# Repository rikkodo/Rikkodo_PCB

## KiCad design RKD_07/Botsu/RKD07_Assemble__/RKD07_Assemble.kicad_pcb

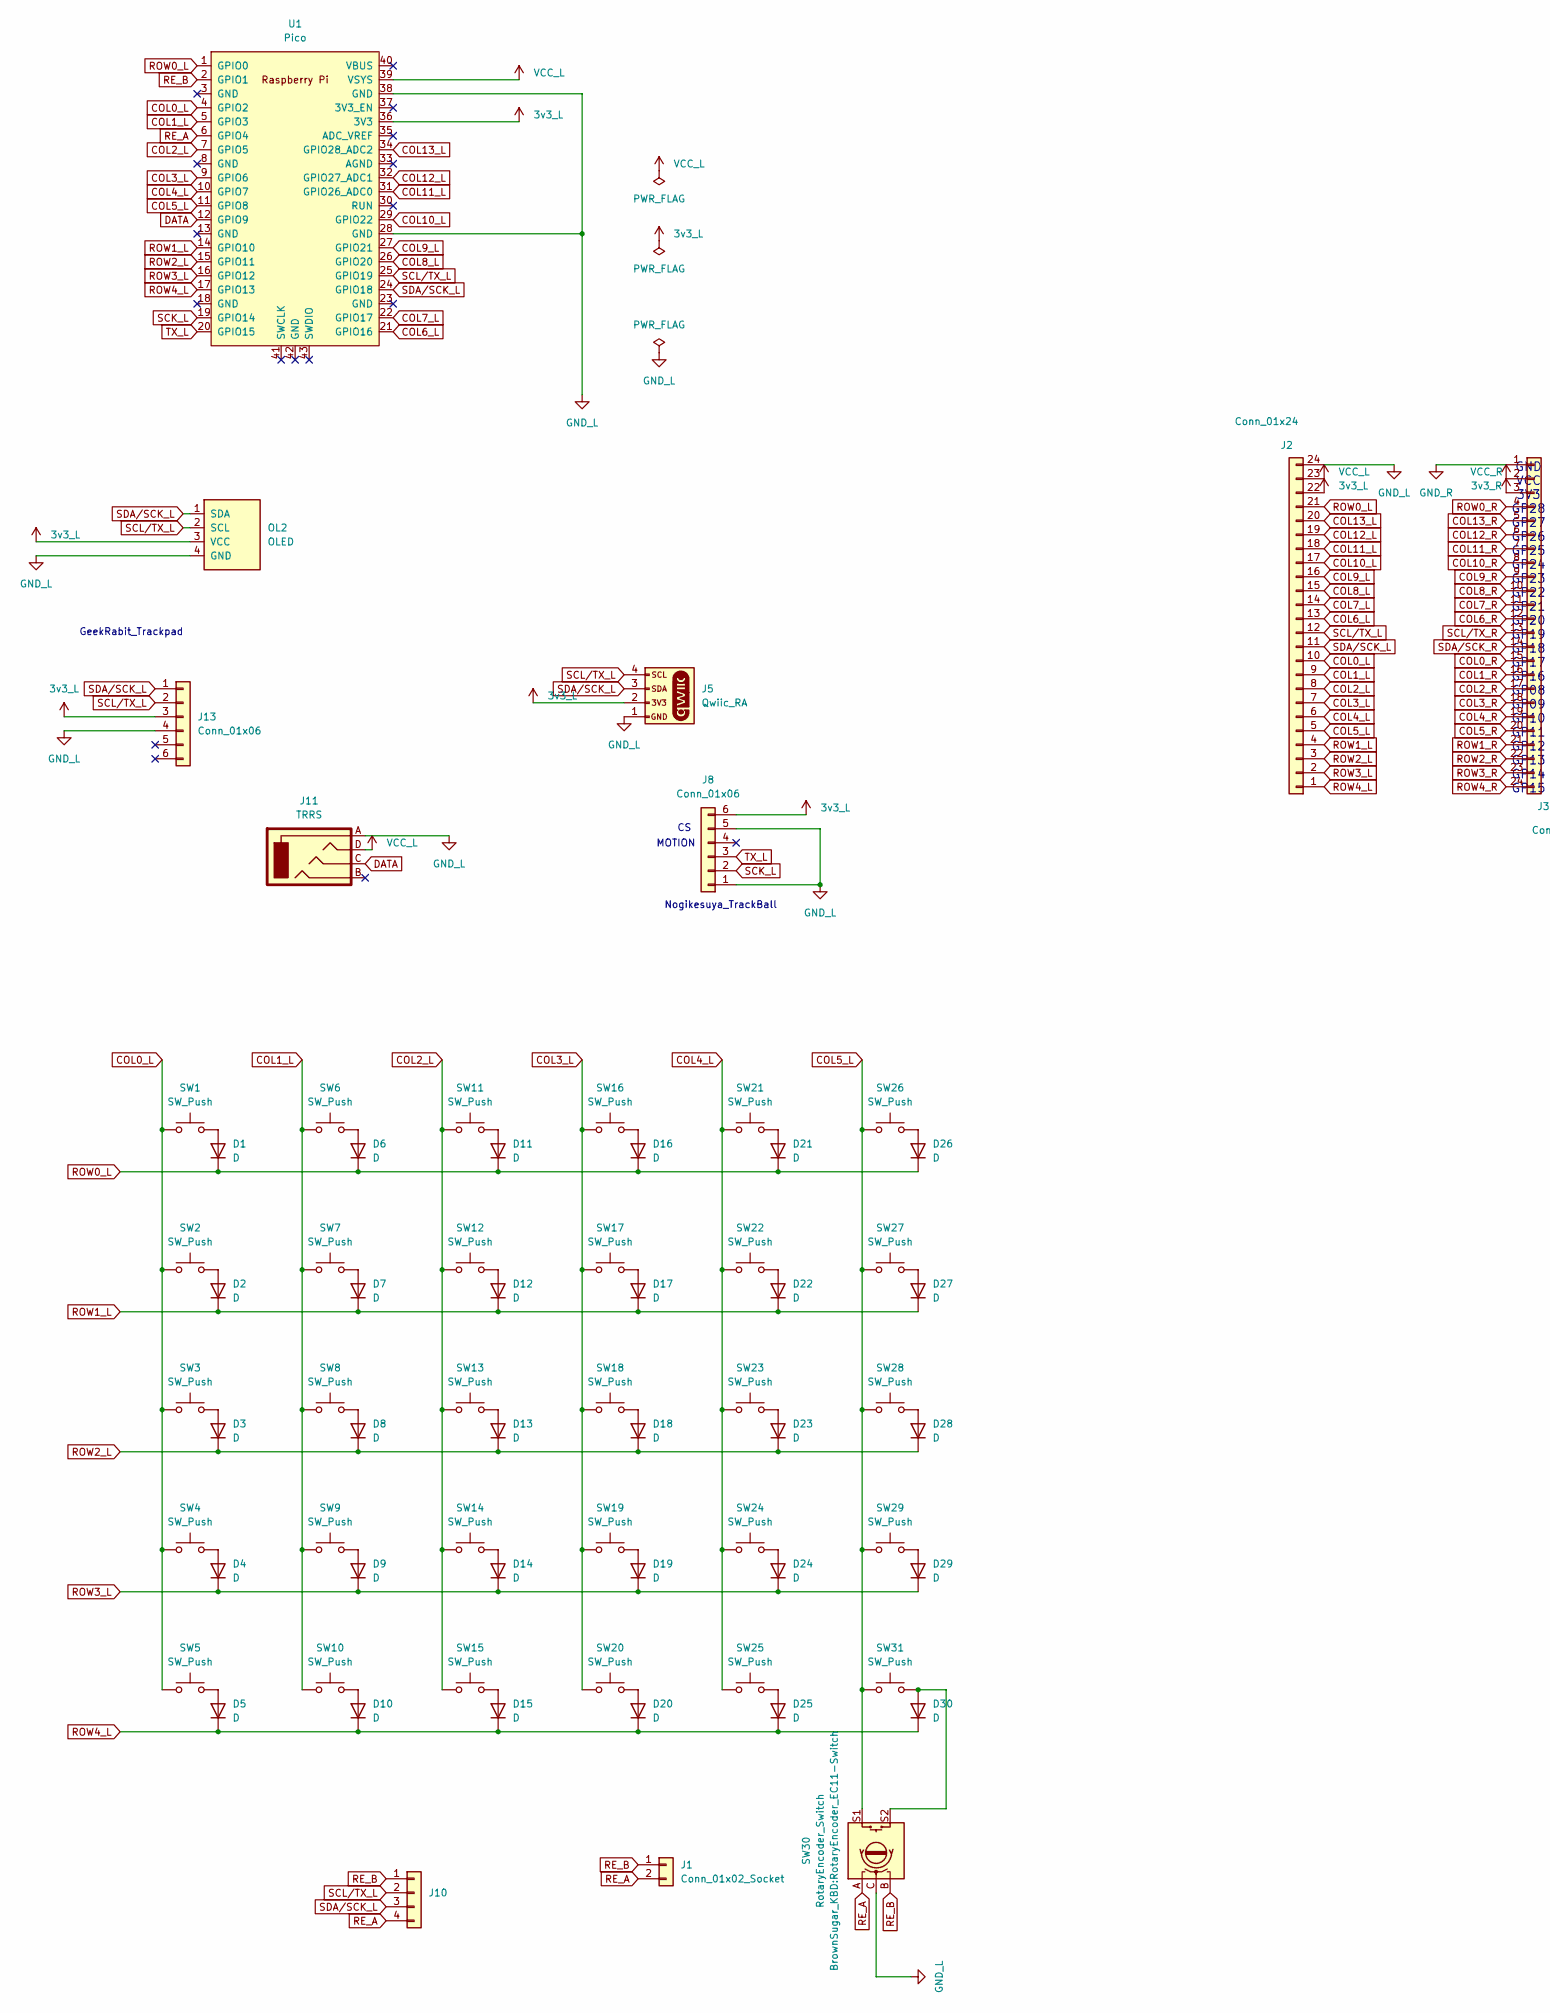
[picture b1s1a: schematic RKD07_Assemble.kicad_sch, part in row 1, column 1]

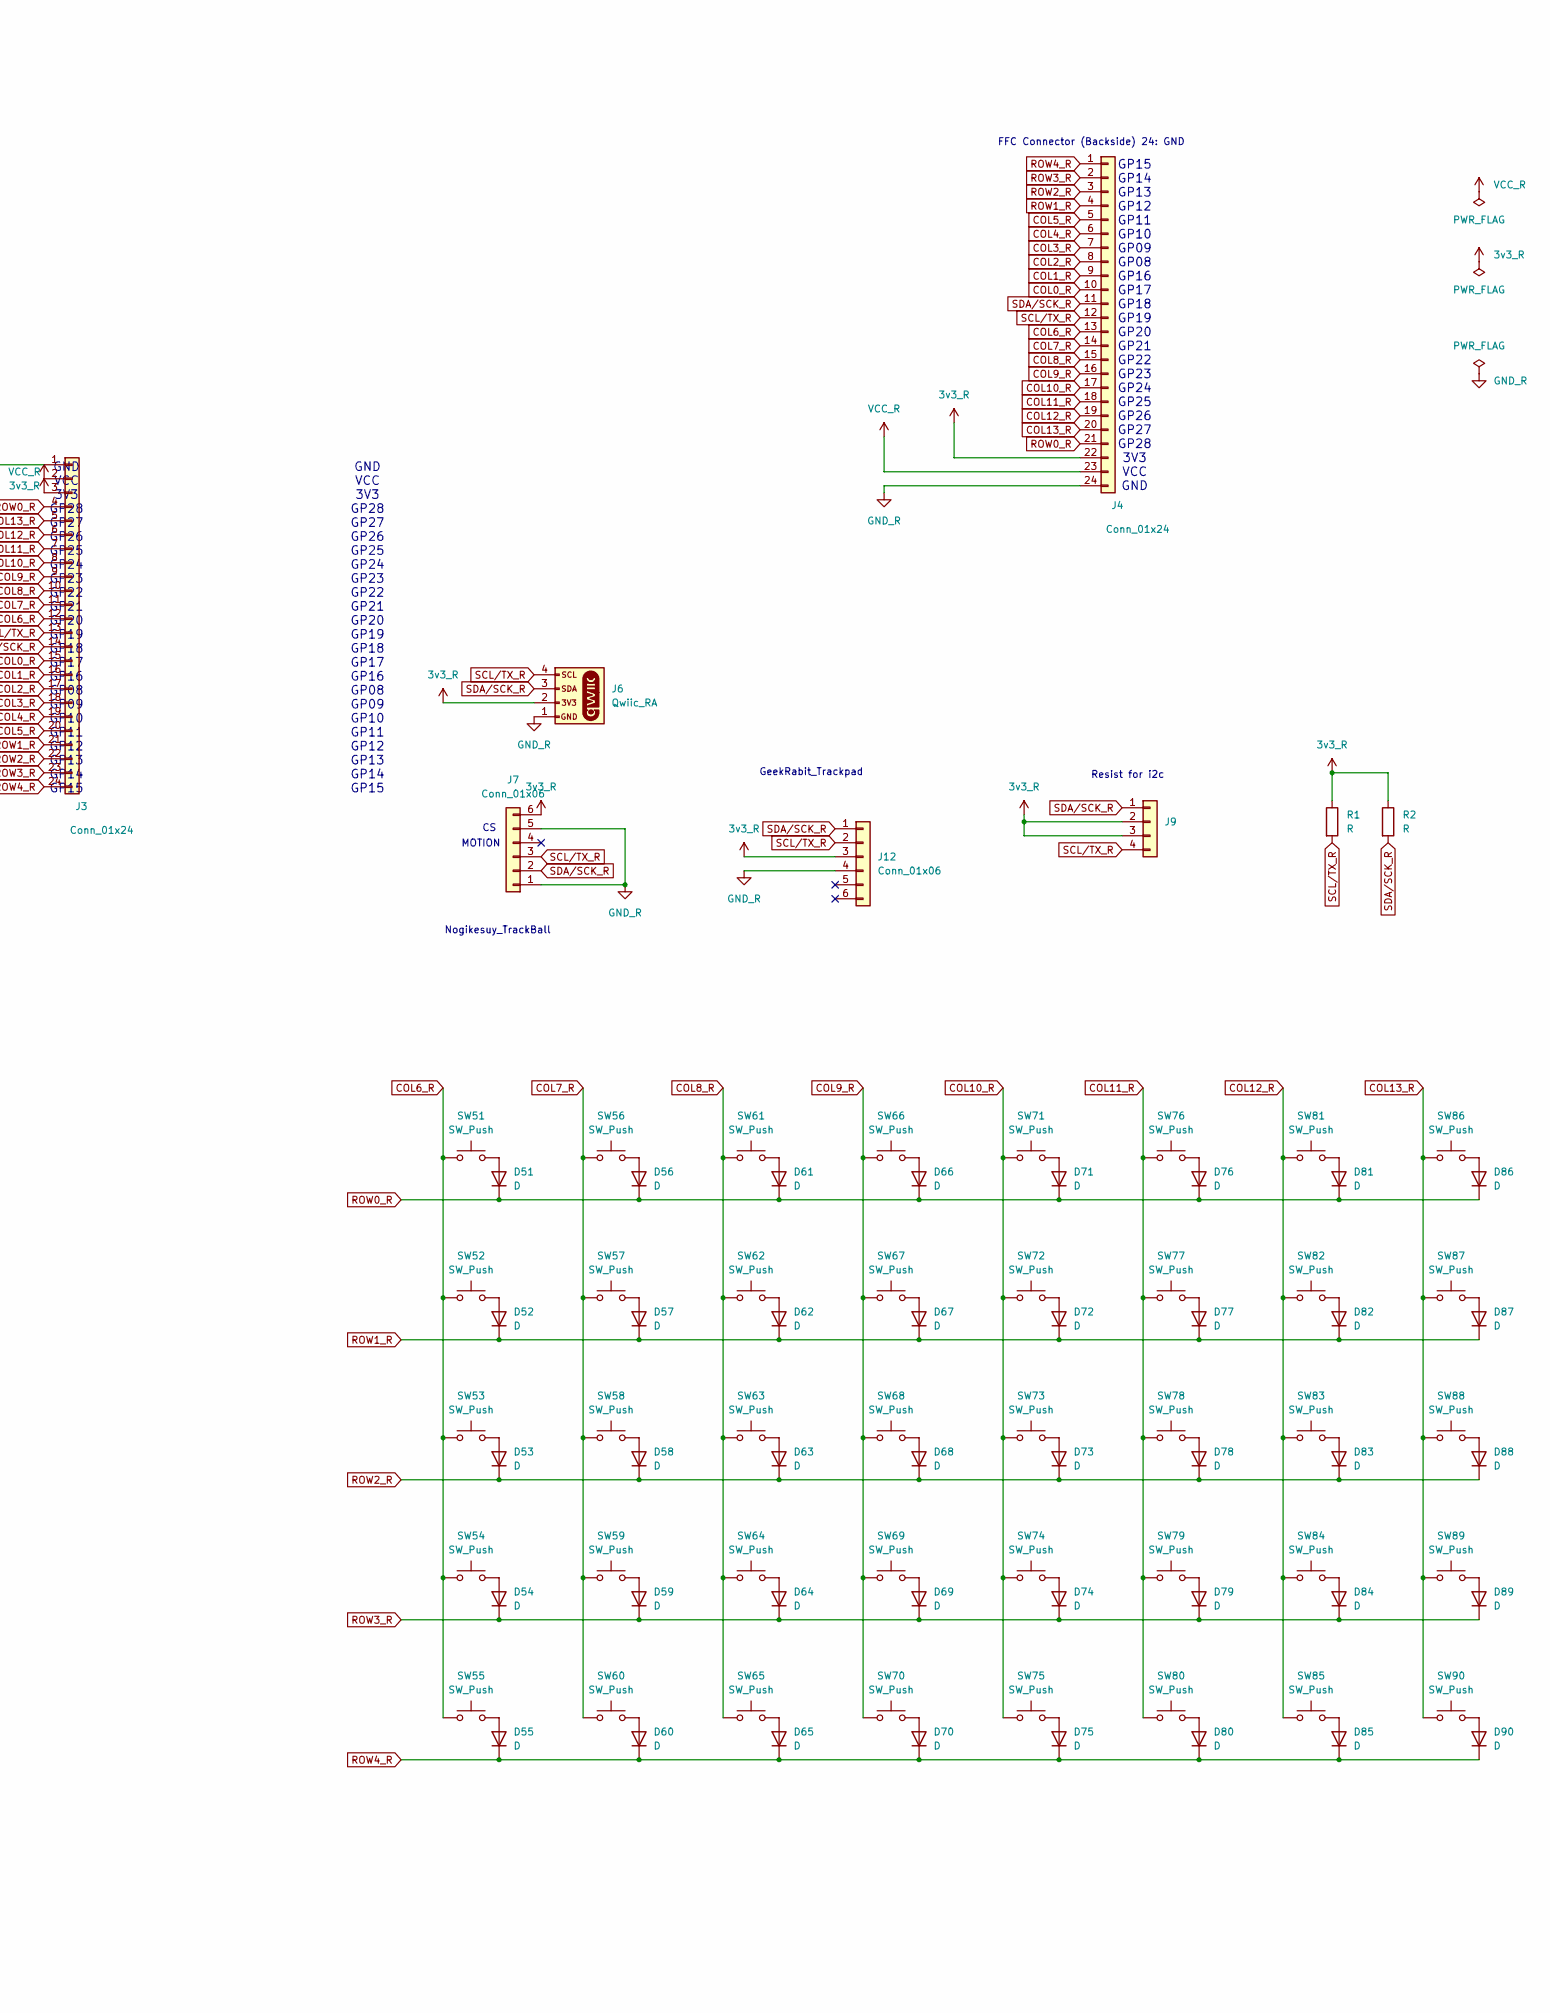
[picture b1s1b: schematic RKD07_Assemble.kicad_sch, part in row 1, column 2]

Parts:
D1, D2, D3, D4, D5, D6, D7, D8, D9, D10, D11, D12, D13, D14, D15, D16, D17, D18, D19, D20, D21, D22, D23, D24, D25, D26, D27, D28, D29, D30, D51, D52, D53, D54, D55, D56, D57, D58, D59, D60, D61, D62, D63, D64, D65, D66, D67, D68, D69, D70, D71, D72, D73, D74, D75, D76, D77, D78, D79, D80, D81, D82, D83, D84, D85, D86, D87, D88, D89, D90: D; Diode_SMD
J1: Conn_01x02_Socket; PinHeader_1x02_P2.54mm_Horizontal
J2, J3, J4: Conn_01x24; Hirose_FH12-24S-0.5SH_1x24-1MP_P0.50mm_Horizontal
J5, J6: Qwiic_RA; JST_SMD_1.0mm-4_Black
J7, J8, J12, J13: Conn_01x06; Hirose_FH12-6S-0.5SH_1x06-1MP_P0.50mm_Horizontal
J9: Conn_01x04; PinSocket_1x04_P2.54mm_Horizontal
J10: Conn_01x04; PinHeader_1x04_P2.54mm_Horizontal
J11: TRRS; TRRS_PJ-320A
OL2: OLED; OLED_center_display
R1, R2: R; R_Axial_DIN0207_L6.3mm_D2.5mm_P10.16mm_Horizontal
SW1, SW2, SW3, SW5, SW6, SW7, SW8, SW9, SW10, SW11, SW12, SW13, SW14, SW15, SW16, SW17, SW18, SW19, SW20, SW21, SW22, SW23, SW24, SW26, SW27, SW28, SW29, SW51, SW52, SW53, SW54, SW55, SW56, SW57, SW58, SW59, SW60, SW61, SW62, SW63, SW64, SW65, SW66, SW67, SW68, SW69, SW70, SW71, SW72, SW73, SW74, SW75, SW76, SW77, SW78, SW79, SW80, SW81, SW82, SW83, SW84, SW85, SW87, SW89, SW90: SW_Push; rkd_Asm_ChocV1V2_Hotswap_1u
SW4, SW25, SW86, SW88: SW_Push; rkd_Asm_ChocV2_Hotswap_2uW
SW30: RotaryEncoder_Switch; RotaryEncoder_EC11-Switch
SW31: SW_Push; ResetSW
U1: Pico; rkd_RPi_Pico_TH_NODBG

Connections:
3v3_L: J2.22, J5.2, J8.6, J13.3, OL2.3 (VCC), U1.36 (3V3)
3v3_R: J3.3, J4.22, J6.2, J7.6, J9.2, J9.3, J12.3, R1.1, R2.1
COL0_L: J2.10, SW1.2, SW2.2, SW3.2, SW4.2, SW5.2, U1.4 (GPIO2)
COL0_R: J3.15, J4.10
COL1_L: J2.9, SW6.2, SW7.2, SW8.2, SW9.2, SW10.2, U1.5 (GPIO3)
COL1_R: J3.16, J4.9
COL2_L: J2.8, SW11.2, SW12.2, SW13.2, SW14.2, SW15.2, U1.7 (GPIO5)
COL2_R: J3.17, J4.8
COL3_L: J2.7, SW16.2, SW17.2, SW18.2, SW19.2, SW20.2, U1.9 (GPIO6)
COL3_R: J3.18, J4.7
COL4_L: J2.6, SW21.2, SW22.2, SW23.2, SW24.2, SW25.2, U1.10 (GPIO7)
COL4_R: J3.19, J4.6
COL5_L: J2.5, SW26.2, SW27.2, SW28.2, SW29.2, SW30.S1, SW31.1, U1.11 (GPIO8)
COL5_R: J3.20, J4.5
COL6_L: J2.13, U1.21 (GPIO16)
COL6_R: J3.12, J4.13, SW51.2, SW52.2, SW53.2, SW54.2, SW55.2
COL7_L: J2.14, U1.22 (GPIO17)
COL7_R: J3.11, J4.14, SW56.2, SW57.2, SW58.2, SW59.2, SW60.2
COL8_L: J2.15, U1.26 (GPIO20)
COL8_R: J3.10, J4.15, SW61.2, SW62.2, SW63.2, SW64.2, SW65.2
COL9_L: J2.16, U1.27 (GPIO21)
COL9_R: J3.9, J4.16, SW66.2, SW67.2, SW68.2, SW69.2, SW70.2
COL10_L: J2.17, U1.29 (GPIO22)
COL10_R: J3.8, J4.17, SW71.2, SW72.2, SW73.2, SW74.2, SW75.2
COL11_L: J2.18, U1.31 (GPIO26_ADC0)
COL11_R: J3.7, J4.18, SW76.2, SW77.2, SW78.2, SW79.2, SW80.2
COL12_L: J2.19, U1.32 (GPIO27_ADC1)
COL12_R: J3.6, J4.19, SW81.2, SW82.2, SW83.2, SW84.2, SW85.2
COL13_L: J2.20, U1.34 (GPIO28_ADC2)
COL13_R: J3.5, J4.20, SW86.2, SW87.2, SW88.2, SW89.2, SW90.2
DATA: J11.C, U1.12 (GPIO9)
GND_L: J2.24, J5.1, J8.1, J8.5, J11.A, J13.4, OL2.4 (GND), SW30.C, U1.28 (GND), U1.38 (GND)
GND_R: J3.1, J4.24, J6.1, J7.1, J7.5, J12.4
unnamed: D1.2 (A), SW1.1
unnamed: D2.2 (A), SW2.1
unnamed: D3.2 (A), SW3.1
unnamed: D4.2 (A), SW4.1
unnamed: D5.2 (A), SW5.1
unnamed: D6.2 (A), SW6.1
unnamed: D7.2 (A), SW7.1
unnamed: D8.2 (A), SW8.1
unnamed: D9.2 (A), SW9.1
unnamed: D10.2 (A), SW10.1
unnamed: D11.2 (A), SW11.1
unnamed: D12.2 (A), SW12.1
unnamed: D13.2 (A), SW13.1
unnamed: D14.2 (A), SW14.1
unnamed: D15.2 (A), SW15.1
unnamed: D16.2 (A), SW16.1
unnamed: D17.2 (A), SW17.1
unnamed: D18.2 (A), SW18.1
unnamed: D19.2 (A), SW19.1
unnamed: D20.2 (A), SW20.1
unnamed: D21.2 (A), SW21.1
unnamed: D22.2 (A), SW22.1
unnamed: D23.2 (A), SW23.1
unnamed: D24.2 (A), SW24.1
unnamed: D25.2 (A), SW25.1
unnamed: D26.2 (A), SW26.1
unnamed: D27.2 (A), SW27.1
unnamed: D28.2 (A), SW28.1
unnamed: D29.2 (A), SW29.1
unnamed: D30.2 (A), SW30.S2, SW31.2
unnamed: D51.2 (A), SW51.1
unnamed: D52.2 (A), SW52.1
unnamed: D53.2 (A), SW53.1
unnamed: D54.2 (A), SW54.1
unnamed: D55.2 (A), SW55.1
unnamed: D56.2 (A), SW56.1
unnamed: D57.2 (A), SW57.1
unnamed: D58.2 (A), SW58.1
unnamed: D59.2 (A), SW59.1
unnamed: D60.2 (A), SW60.1
unnamed: D61.2 (A), SW61.1
unnamed: D62.2 (A), SW62.1
unnamed: D63.2 (A), SW63.1
unnamed: D64.2 (A), SW64.1
unnamed: D65.2 (A), SW65.1
unnamed: D66.2 (A), SW66.1
unnamed: D67.2 (A), SW67.1
unnamed: D68.2 (A), SW68.1
unnamed: D69.2 (A), SW69.1
unnamed: D70.2 (A), SW70.1
unnamed: D71.2 (A), SW71.1
unnamed: D72.2 (A), SW72.1
unnamed: D73.2 (A), SW73.1
unnamed: D74.2 (A), SW74.1
unnamed: D75.2 (A), SW75.1
unnamed: D76.2 (A), SW76.1
unnamed: D77.2 (A), SW77.1
unnamed: D78.2 (A), SW78.1
unnamed: D79.2 (A), SW79.1
unnamed: D80.2 (A), SW80.1
unnamed: D81.2 (A), SW81.1
unnamed: D82.2 (A), SW82.1
unnamed: D83.2 (A), SW83.1
unnamed: D84.2 (A), SW84.1
unnamed: D85.2 (A), SW85.1
unnamed: D86.2 (A), SW86.1
unnamed: D87.2 (A), SW87.1
unnamed: D88.2 (A), SW88.1
unnamed: D89.2 (A), SW89.1
unnamed: D90.2 (A), SW90.1
RE_A: J1.2, J10.4, SW30.A, U1.6 (GPIO4)
RE_B: J1.1, J10.1, SW30.B, U1.2 (GPIO1)
ROW0_L: D1.1 (K), D6.1 (K), D11.1 (K), D16.1 (K), D21.1 (K), D26.1 (K), J2.21, U1.1 (GPIO0)
ROW0_R: D51.1 (K), D56.1 (K), D61.1 (K), D66.1 (K), D71.1 (K), D76.1 (K), D81.1 (K), D86.1 (K), J3.4, J4.21
ROW1_L: D2.1 (K), D7.1 (K), D12.1 (K), D17.1 (K), D22.1 (K), D27.1 (K), J2.4, U1.14 (GPIO10)
ROW1_R: D52.1 (K), D57.1 (K), D62.1 (K), D67.1 (K), D72.1 (K), D77.1 (K), D82.1 (K), D87.1 (K), J3.21, J4.4
ROW2_L: D3.1 (K), D8.1 (K), D13.1 (K), D18.1 (K), D23.1 (K), D28.1 (K), J2.3, U1.15 (GPIO11)
ROW2_R: D53.1 (K), D58.1 (K), D63.1 (K), D68.1 (K), D73.1 (K), D78.1 (K), D83.1 (K), D88.1 (K), J3.22, J4.3
ROW3_L: D4.1 (K), D9.1 (K), D14.1 (K), D19.1 (K), D24.1 (K), D29.1 (K), J2.2, U1.16 (GPIO12)
ROW3_R: D54.1 (K), D59.1 (K), D64.1 (K), D69.1 (K), D74.1 (K), D79.1 (K), D84.1 (K), D89.1 (K), J3.23, J4.2
ROW4_L: D5.1 (K), D10.1 (K), D15.1 (K), D20.1 (K), D25.1 (K), D30.1 (K), J2.1, U1.17 (GPIO13)
ROW4_R: D55.1 (K), D60.1 (K), D65.1 (K), D70.1 (K), D75.1 (K), D80.1 (K), D85.1 (K), D90.1 (K), J3.24, J4.1
SCK_L: J8.2, U1.19 (GPIO14)
SCL/TX_L: J2.12, J5.4, J10.2, J13.2, OL2.2 (SCL), U1.25 (GPIO19)
SCL/TX_R: J3.13, J4.12, J6.4, J7.3, J9.4, J12.2, R1.2
SDA/SCK_L: J2.11, J5.3, J10.3, J13.1, OL2.1 (SDA), U1.24 (GPIO18)
SDA/SCK_R: J3.14, J4.11, J6.3, J7.2, J9.1, J12.1, R2.2
TX_L: J8.3, U1.20 (GPIO15)
VCC_L: J2.23, J11.D, U1.39 (VSYS)
VCC_R: J3.2, J4.23

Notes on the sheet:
GND VCC 3V3 GP28 GP27 GP26 GP25 GP24 GP23 GP22 GP21 GP20 GP19 GP18 GP17 GP16 GP08 GP09 GP10 GP11 GP12 GP13 GP14 GP15
Nogikesuy_TrackBall
GeekRabit_Trackpad
MOTION
Resist for i2c
FFC Connector (Backside) 24: GND
GP15 GP14 GP13 GP12 GP11 GP10 GP09 GP08 GP16 GP17 GP18 GP19 GP20 GP21 GP22 GP23 GP24 GP25 GP26 GP27 GP28 3V3 VCC GND
Nogikesuya_TrackBall

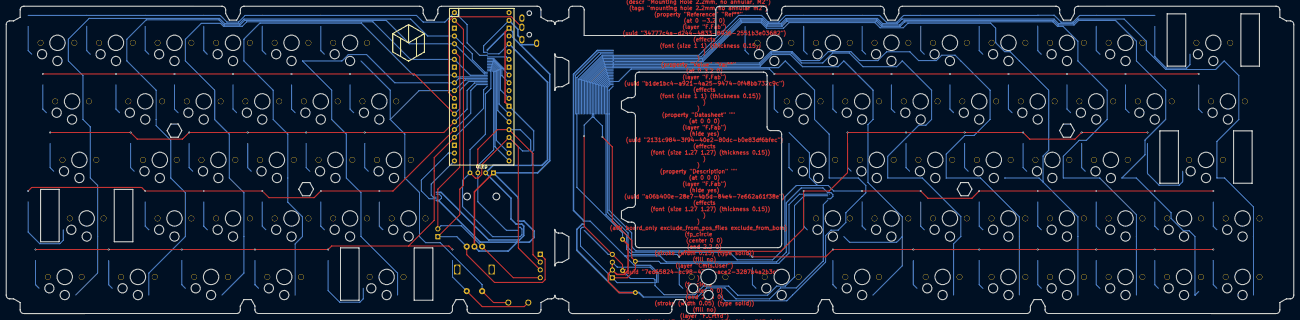
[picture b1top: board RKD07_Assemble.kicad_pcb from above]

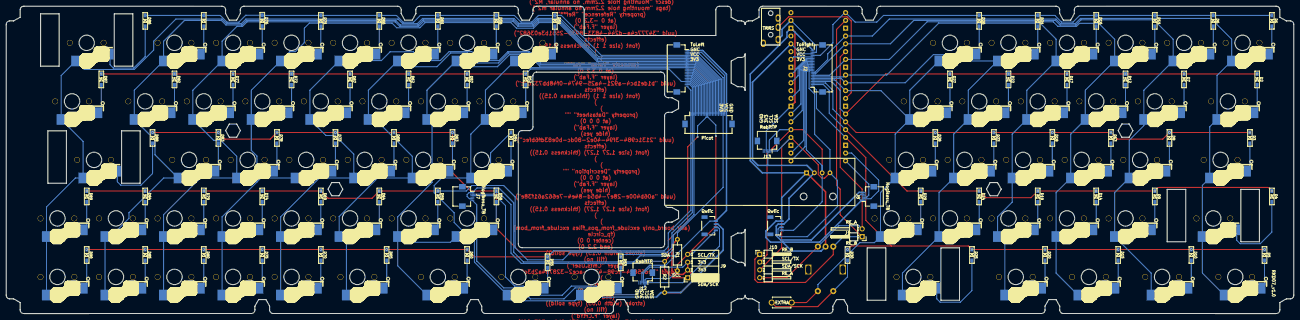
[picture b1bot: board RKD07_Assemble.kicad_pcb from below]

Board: 2 copper layers, 419.1 x 100.0 mm, 164 parts (15 on the bottom side), 123 nets.

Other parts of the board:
M3, M4, M5, M6: Mark; m2_Spacer_Hole_hex
M8: Mark; rkd_LOGO_2x
Point1: Guard_Screw_Hall; rkd_Guard_Screw_Hall
